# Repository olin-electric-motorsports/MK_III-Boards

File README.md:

# MK_III-Boards
Kicad files for our boards for the 2017-2018 Competition season.

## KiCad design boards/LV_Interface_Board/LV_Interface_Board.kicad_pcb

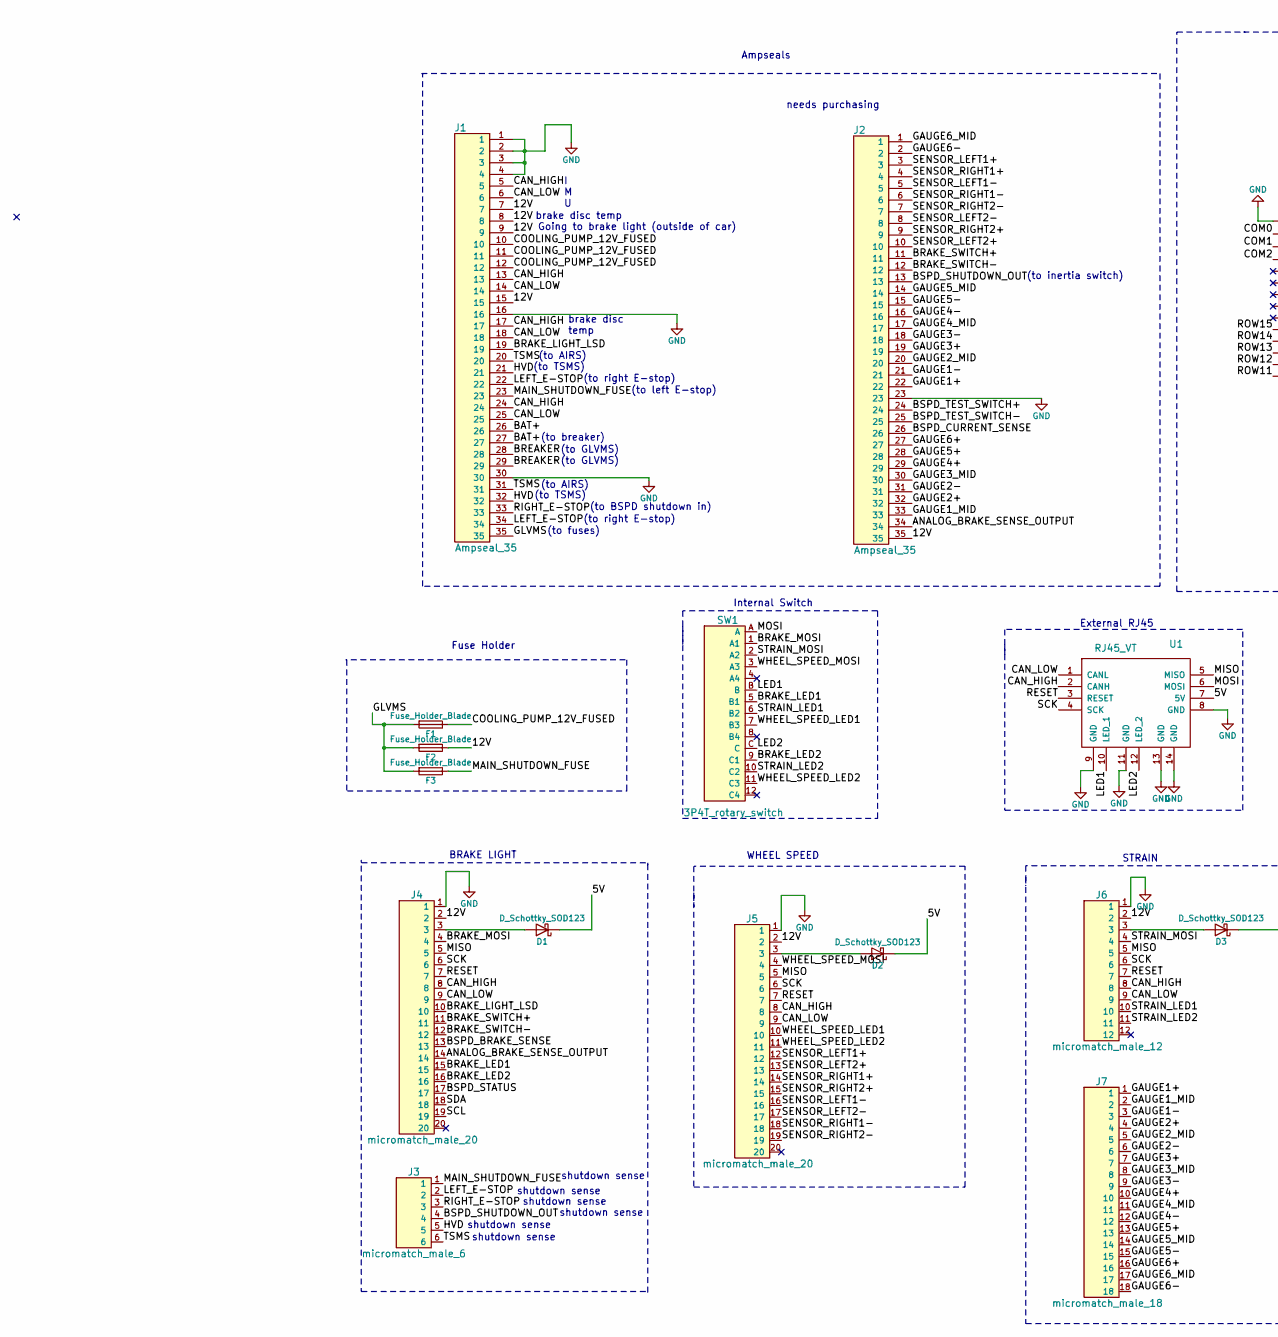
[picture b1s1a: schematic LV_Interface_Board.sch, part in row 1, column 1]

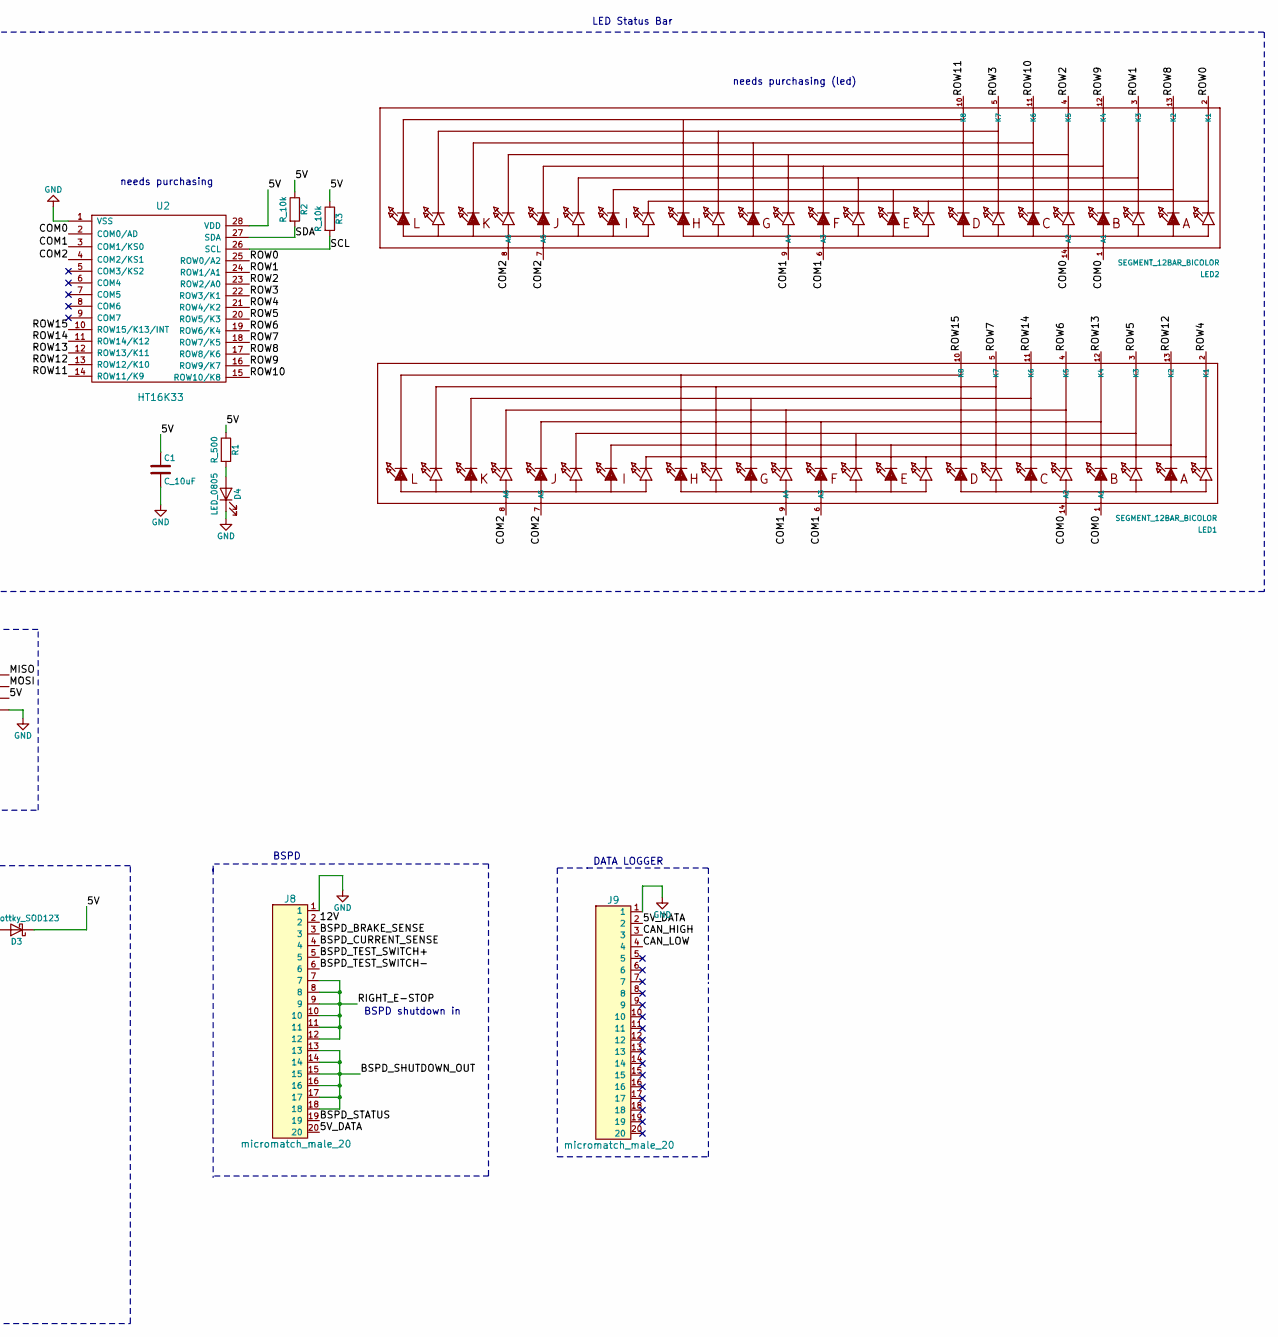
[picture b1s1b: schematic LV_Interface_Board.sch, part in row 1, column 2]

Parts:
C1: C_10uF; C_0805_OEM; MPN 478-5167-1-ND
D1, D2, D3: D_Schottky_SOD123; D_SOD-123W_OEM; MPN 1727-2394-1-ND
D4: LED_0805; LED_0805_OEM; MPN 475-1410-1-ND
F1, F2, F3: Fuse_Holder_Blade; fuse_block_holder; MPN 36-3557-2-ND
J1, J2: Ampseal_35
J3: micromatch_male_6; micromatch_female_ra_6; MPN A107035CT-ND
J4, J5, J8, J9: micromatch_male_20; micromatch_female_ra_20; MPN A111126CT-ND
J6: micromatch_male_12; micromatch_female_ra_12; MPN A110882CT-ND
J7: micromatch_male_18; micromatch_female_ra_18; MPN A110884CT-ND
LED1, LED2: SEGMENT_12BAR_BICOLOR; SEGMENT_BICOL_BL-AR12Z3010
R1: R_500; R_0805_OEM; MPN 541-1905-2-ND
R2, R3: R_10k; R_0805_OEM; MPN CRS0805-FX-1002ELFCT-ND
SW1: 3P4T_rotary_switch; MPN s14100400am2451
U1: RJ45_VT; RJ45-Vertical
U2: HT16K33; SOP28

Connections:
/5V: C1.1, D1.1 (K), D2.1 (K), D3.1 (K), R1.1, R2.1, R3.1, U1.7 (5V), U2.28 (VDD)
/5V_DATA: J8.20, J9.2
/12V: F2.1, J1.7, J1.8, J1.9, J1.15, J2.35, J4.2, J5.2, J6.2, J8.2
/ANALOG_BRAKE_SENSE_OUTPUT: J2.34, J4.14
/BAT+: J1.26, J1.27
/BRAKE_LED1: J4.15, SW1.5 (B1)
/BRAKE_LED2: J4.16, SW1.9 (C1)
/BRAKE_LIGHT_LSD: J1.19, J4.10
/BRAKE_MOSI: J4.4, SW1.1 (A1)
/BRAKE_SWITCH+: J2.11, J4.11
/BRAKE_SWITCH-: J2.12, J4.12
/BREAKER: J1.28, J1.29
/BSPD_BRAKE_SENSE: J4.13, J8.3
/BSPD_CURRENT_SENSE: J2.26, J8.4
/BSPD_SHUTDOWN_OUT: J2.13, J3.4, J8.13, J8.14, J8.15, J8.16, J8.17, J8.18
/BSPD_STATUS: J4.17, J8.19
/BSPD_TEST_SWITCH+: J2.24, J8.5
/BSPD_TEST_SWITCH-: J2.25, J8.6
/CAN_HIGH: J1.5, J1.13, J1.17, J1.24, J4.8, J5.8, J6.8, J9.3, U1.2 (CANH)
/CAN_LOW: J1.6, J1.14, J1.18, J1.25, J4.9, J5.9, J6.9, J9.4, U1.1 (CANL)
/COM0: LED1.1 (A1), LED1.14 (A2), LED2.1 (A1), LED2.14 (A2), U2.2 (COM0/AD)
/COM1: LED1.6 (A3), LED1.9 (A4), LED2.6 (A3), LED2.9 (A4), U2.3 (COM1/KS0)
/COM2: LED1.7 (A5), LED1.8 (A6), LED2.7 (A5), LED2.8 (A6), U2.4 (COM2/KS1)
/COOLING_PUMP_12V_FUSED: F1.1, J1.10, J1.11, J1.12
/GAUGE1+: J2.22, J7.1
/GAUGE1-: J2.21, J7.3
/GAUGE1_MID: J2.33, J7.2
/GAUGE2+: J2.32, J7.4
/GAUGE2-: J2.31, J7.6
/GAUGE2_MID: J2.20, J7.5
/GAUGE3+: J2.19, J7.7
/GAUGE3-: J2.18, J7.9
/GAUGE3_MID: J2.30, J7.8
/GAUGE4+: J2.29, J7.10
/GAUGE4-: J2.16, J7.12
/GAUGE4_MID: J2.17, J7.11
/GAUGE5+: J2.28, J7.13
/GAUGE5-: J2.15, J7.15
/GAUGE5_MID: J2.14, J7.14
/GAUGE6+: J2.27, J7.16
/GAUGE6-: J2.2, J7.18
/GAUGE6_MID: J2.1, J7.17
/GLVMS: F1.2, F2.2, F3.2, J1.35
/HVD: J1.21, J1.32, J3.5
/LED1: SW1.B, U1.10 (LED_1)
/LED2: SW1.C, U1.12 (LED_2)
/LEFT_E-STOP: J1.22, J1.34, J3.2
/MAIN_SHUTDOWN_FUSE: F3.1, J1.23, J3.1
/MISO: J4.5, J5.5, J6.5, U1.5 (MISO)
/MOSI: SW1.A, U1.6 (MOSI)
/RESET: J4.7, J5.7, J6.7, U1.3 (RESET)
/RIGHT_E-STOP: J1.33, J3.3, J8.7, J8.8, J8.9, J8.10, J8.11, J8.12
/ROW0: LED2.2 (K1), U2.25 (ROW0/A2)
/ROW1: LED2.3 (K3), U2.24 (ROW1/A1)
/ROW2: LED2.4 (K5), U2.23 (ROW2/A0)
/ROW3: LED2.5 (K7), U2.22 (ROW3/K1)
/ROW4: LED1.2 (K1), U2.21 (ROW4/K2)
/ROW5: LED1.3 (K3), U2.20 (ROW5/K3)
/ROW6: LED1.4 (K5), U2.19 (ROW6/K4)
/ROW7: LED1.5 (K7), U2.18 (ROW7/K5)
/ROW8: LED2.13 (K2), U2.17 (ROW8/K6)
/ROW9: LED2.12 (K4), U2.16 (ROW9/K7)
/ROW10: LED2.11 (K6), U2.15 (ROW10/K8)
/ROW11: LED2.10 (K8), U2.14 (ROW11/K9)
/ROW12: LED1.13 (K2), U2.13 (ROW12/K10)
/ROW13: LED1.12 (K4), U2.12 (ROW13/K11)
/ROW14: LED1.11 (K6), U2.11 (ROW14/K12)
/ROW15: LED1.10 (K8), U2.10 (ROW15/K13/INT)
/SCK: J4.6, J5.6, J6.6, U1.4 (SCK)
/SCL: J4.19, R3.2, U2.26 (SCL)
/SDA: J4.18, R2.2, U2.27 (SDA)
/SENSOR_LEFT1+: J2.3, J5.12
/SENSOR_LEFT1-: J2.5, J5.16
/SENSOR_LEFT2+: J2.10, J5.13
/SENSOR_LEFT2-: J2.8, J5.17
/SENSOR_RIGHT1+: J2.4, J5.14
/SENSOR_RIGHT1-: J2.6, J5.18
/SENSOR_RIGHT2+: J2.9, J5.15
/SENSOR_RIGHT2-: J2.7, J5.19
/STRAIN_LED1: J6.10, SW1.6 (B2)
/STRAIN_LED2: J6.11, SW1.10 (C2)
/STRAIN_MOSI: J6.4, SW1.2 (A2)
/TSMS: J1.20, J1.31, J3.6
/WHEEL_SPEED_LED1: J5.10, SW1.7 (B3)
/WHEEL_SPEED_LED2: J5.11, SW1.11 (C3)
/WHEEL_SPEED_MOSI: J5.4, SW1.3 (A3)
GND: C1.2, D4.1 (K), J1.1, J1.2, J1.3, J1.4, J1.16, J1.30, J2.23, J4.1, J5.1, J6.1, J8.1, J9.1, U1.8 (GND), U1.9 (GND), U1.11 (GND), U1.13 (GND), U1.14 (GND), U2.1 (VSS)
unnamed: D1.2 (A), J4.3
unnamed: D2.2 (A), J5.3
unnamed: D3.2 (A), J6.3
unnamed: D4.2 (A), R1.2

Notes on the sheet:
DATA LOGGER
STRAIN
BSPD
WHEEL SPEED
BRAKE LIGHT
Internal Switch
External RJ45
(to inertia switch)
(to breaker)
(to GLVMS) (to GLVMS)
(to left E-stop)
(to right E-stop)
(to TSMS)
(to AIRS)
(to BSPD shutdown in)
(to fuses)
shutdown sense
brake disc temp
I M U
brake disc temp
Fuse Holder
Going to brake light (outside of car)
Ampseals
LED Status Bar
BSPD shutdown in
needs purchasing
needs purchasing (led)

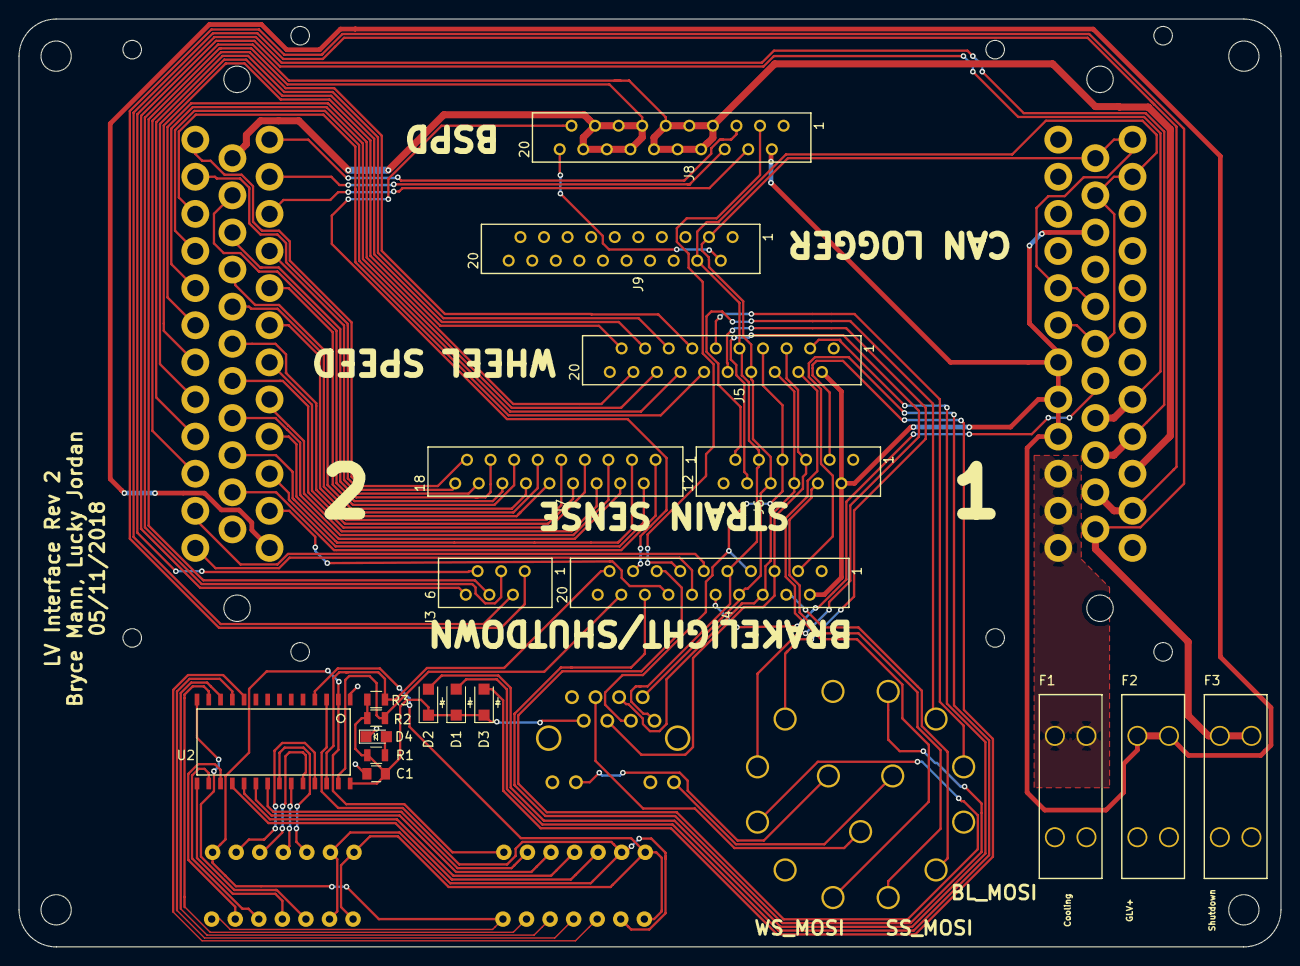
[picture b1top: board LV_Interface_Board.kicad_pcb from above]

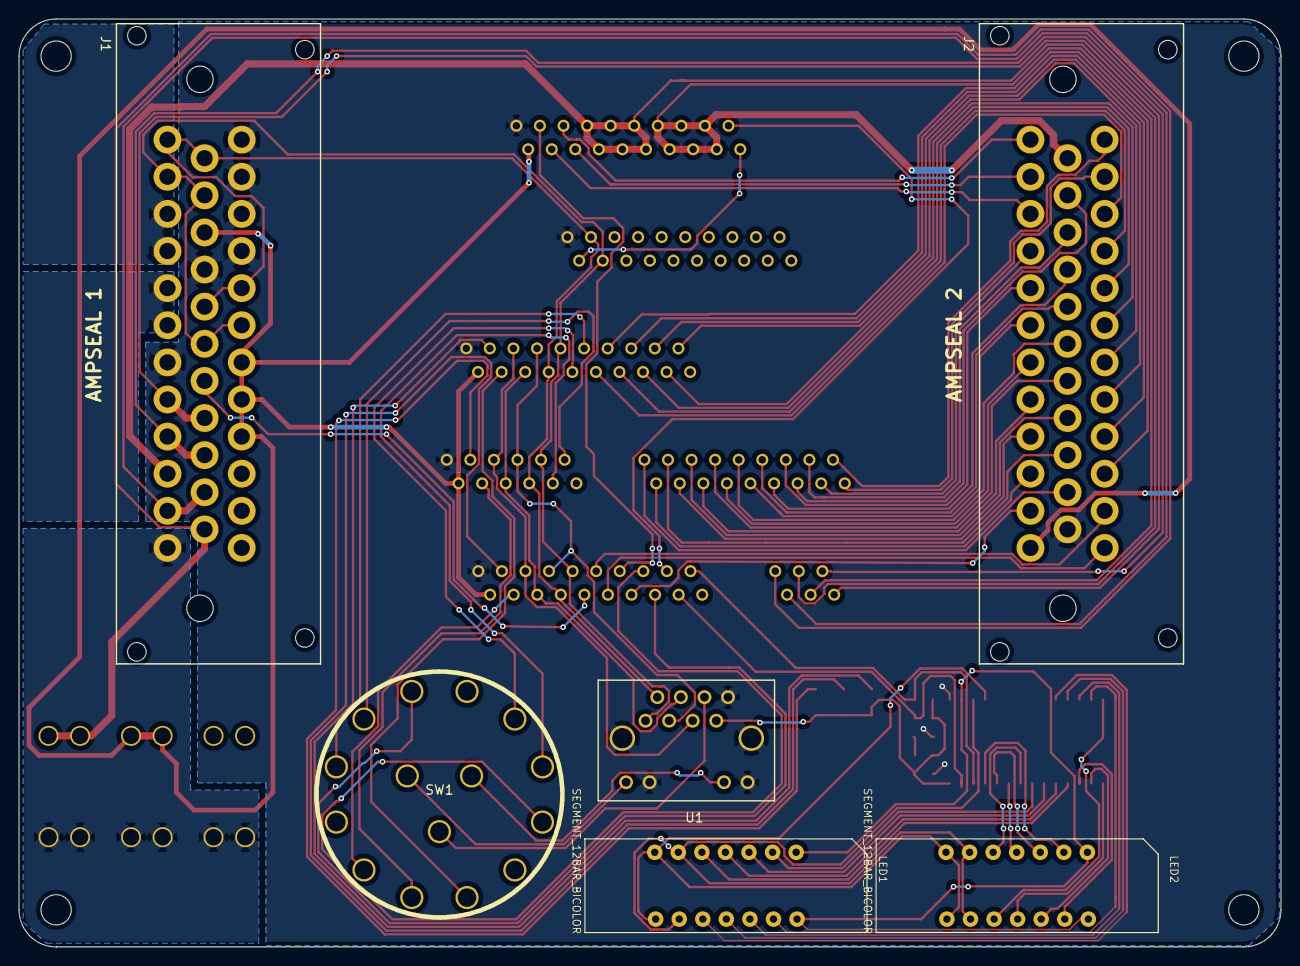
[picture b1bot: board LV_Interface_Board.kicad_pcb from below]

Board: 2 copper layers, 136.0 x 100.0 mm, 25 parts (6 on the bottom side), 91 nets.

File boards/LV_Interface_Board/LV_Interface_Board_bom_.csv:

Component,Description,Part,References,Value,Footprint,Quantity Per PCB,Datasheet,Package,MPN,MFN,PurchasingLink
1,CAP CER 10UF 10V X5R 0805,C_10uF,C1,C_10uF,C_0805_OEM,1,http://datasheets.avx.com/cx5r.pdf,Value,478-5167-1-ND,Digi-Key,https://www.digikey.com/product-detail/en/avx-corporation/08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
2,DIODE SCHOTTKY 100V 1A SOD123,D_Schottky_SOD123,D1 D2 D3,D_Schottky_SOD123,D_SOD-123W_OEM,3,https://assets.nexperia.com/documents/data-sheet/PMEG10010ELR.pdf,,1727-2394-1-ND,Digi-Key,https://www.digikey.com/product-detail/en/nexperia-usa-inc/P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
3,LED_0805,LED_0805,D4,LED_0805,LED_0805_OEM,1,http://www.osram-os.com/Graphics/XPic9/00078860_0.pdf,Value,475-1410-1-ND,Digi-Key,https://www.digikey.com/products/en?keywords=475-1410-1-ND
4,fuse block,fuse_holder_125V_15A,F1,fuse_holder_125V_15A,fuse_block,1,http://www.littelfuse.com/~/media/electronics/datasheets/res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,Value,F5764CT-ND,Digi-Key,https://www.digikey.com/products/en/circuit-protection/fuseh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
5,Waterproof Panel-Mount Connector RA 35-Pin,Ampseal_35,J1 J2,Ampseal_35,Ampseal_35,2,http://www.te.com/commerce/DocumentDelivery/DDEController?Ac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,,,,
6,connector micromatch male 12,micromatch_male_12,J6,micromatch_male_12,micromatch_female_ra_12,1,,Value,A110882CT-ND,Digi-Key,https://www.digikey.com/product-detail/en/te-connectivity-am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
7,connector micromatch male 18,micromatch_male_18,J7,micromatch_male_18,micromatch_female_ra_18,1,,Value,A110884CT-ND,Digi-Key,https://www.digikey.com/product-detail/en/te-connectivity-am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
8,connector micromatch male 20,micromatch_male_20,J4 J5 J8 J9,micromatch_male_20,micromatch_female_ra_20,4,,Value,A111126CT-ND,Digi-Key,https://www.digikey.com/product-detail/en/te-connectivity-am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
9,connector micromatch male 6,micromatch_male_6,J3,micromatch_male_6,micromatch_female_ra_6,1,,Value,A107035CT-ND,Digi-Key,https://www.digikey.com/product-detail/en/te-connectivity-am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
10,,SEGMENT_12BAR_BICOLOR,LED1 LED2,SEGMENT_12BAR_BICOLOR,SEGMENT_BICOL_BL-AR12Z3010,2,,,,,
11,Res 10k 1%,R_10k,R2 R3,R_10k,R_0805_OEM,2,http://www.bourns.com/data/global/pdfs/CRS.pdf,Value,CRS0805-FX-1002ELFCT-ND,Digi-Key,https://www.digikey.com/products/en?keywords=CRS0805-FX-1002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
12,Resistor 500Ohm 0.1% Tolerance,R_500,R1,R_500,R_0805_OEM,1,http://www.vishay.com/docs/60057/pnm.pdf,Value,541-1905-2-ND,Digi Key,https://www.digikey.com/product-detail/en/vishay-dale/PNM040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
13,3P4T rotary switch,3P4T_rotary_switch,SW1,3P4T_rotary_switch,3P4T_rotary_switch,1,,Value,s14100400am2451,Uxcell,https://www.amazon.com/Single-Rotary-Switch-Selector-Positio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
14,,HT16K33,U2,HT16K33,SOP28,1,,,,,
15,CONN MOD JACK 8P8C VERT UNSHLD,RJ45_VT,U1,RJ45_VT,RJ45-Vertical,1,https://www.amphenolcanada.com/ProductSearch/drawings/AC/MRJ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,,,,https://www.digikey.com/products/en?keywords=MRJ-5481-01





Component Groups:,15
Component Count:,23
Fitted Components:,23
Number of PCBs:,1
Total components:,23
Schematic Version:,
Schematic Date:,
BoM Date:,Mon 26 Feb 2018 10:05:01 PM EST
Schematic Source:,/home/bryce/Storage/Formula/Boards/boards/LV_Interface_Board/LV_Interface_Board.sch
KiCad Version:,Eeschema 4.0.2+dfsg1-stable

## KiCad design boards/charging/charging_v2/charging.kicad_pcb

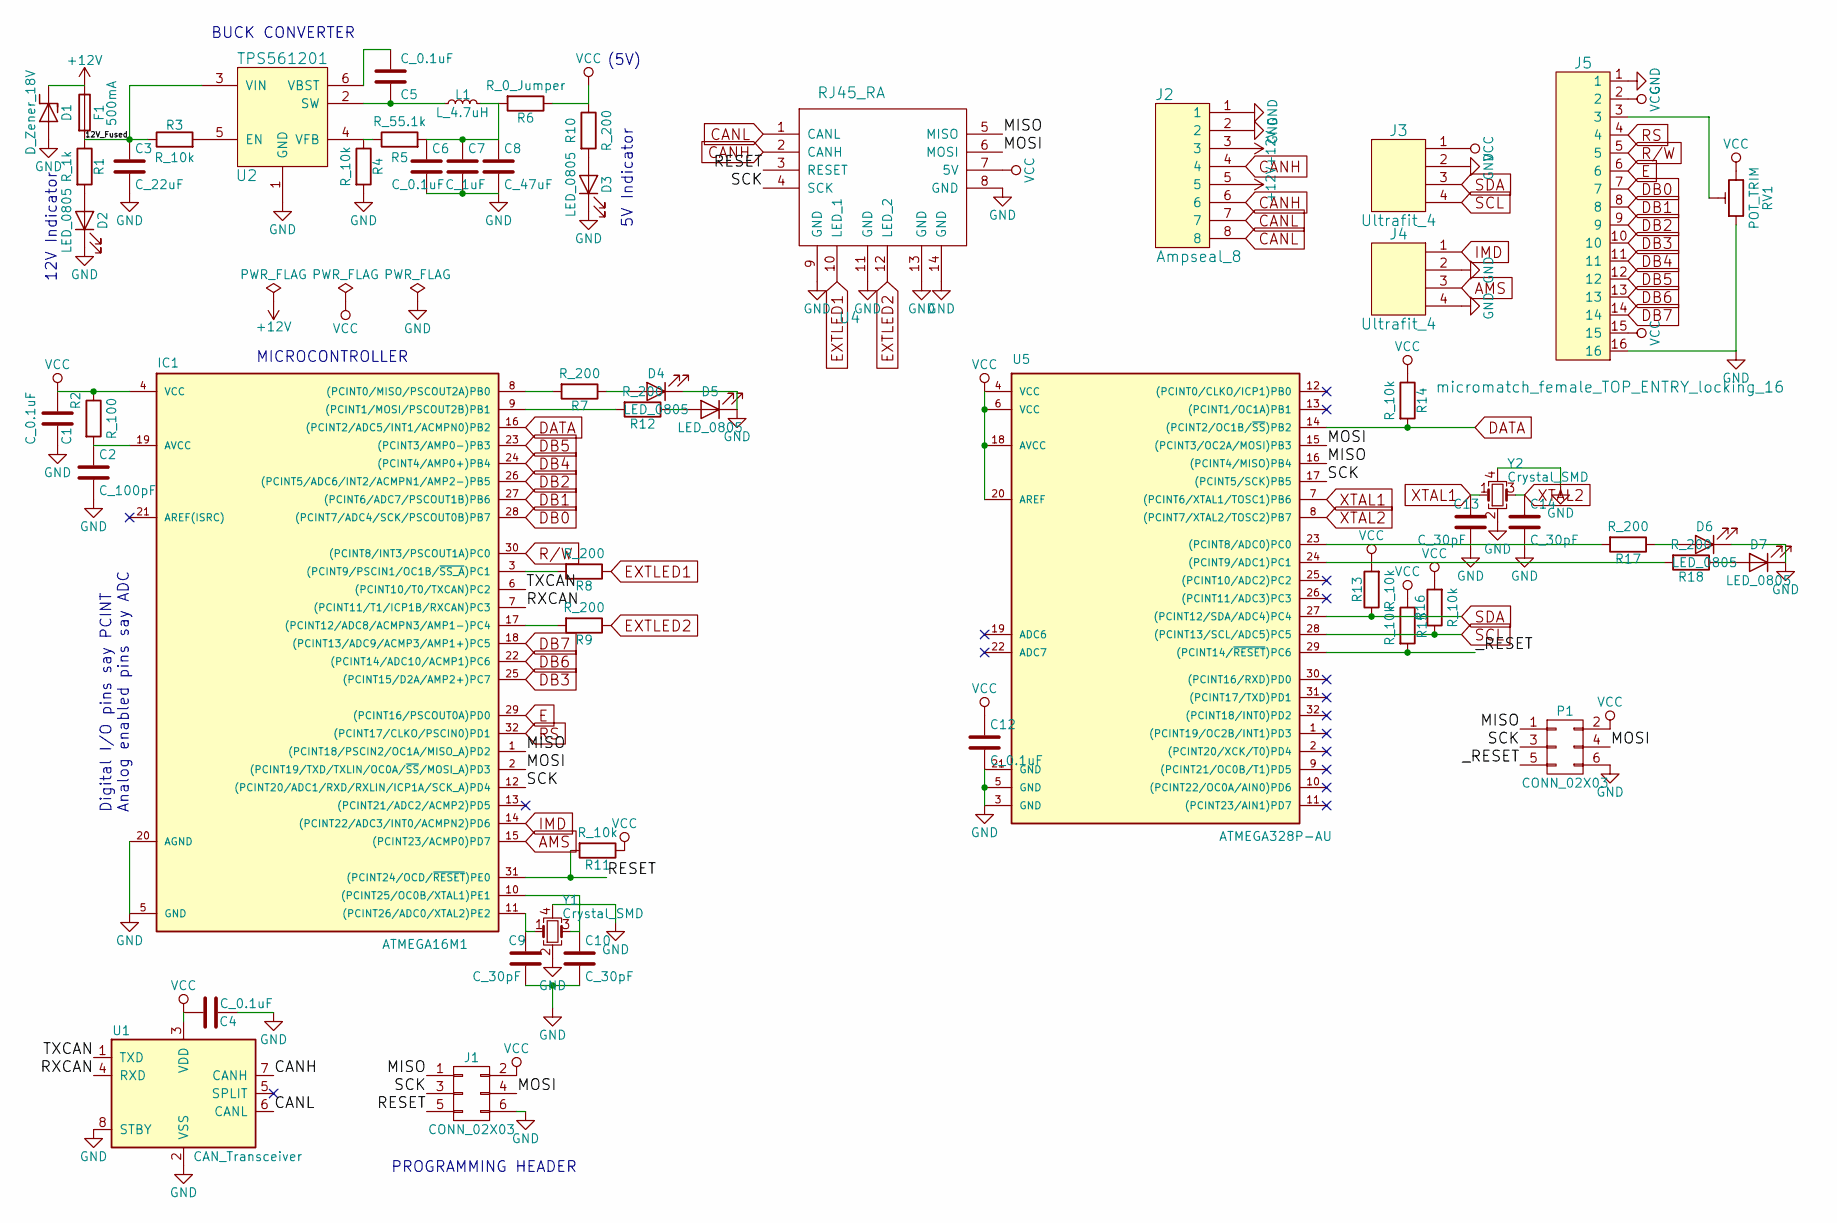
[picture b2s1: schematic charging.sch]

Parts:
C1, C4, C5: C_0.1uF; C_0805; MPN 478-3352-1-ND
C2: C_100pF; C_0805; MPN 399-1122-1-ND
C3: C_22uF; C_1206; MPN 1276-2725-1-ND
C6, C12: C_0.1uF; C_0805_OEM; MPN 478-3352-1-ND
C7: C_1uF; C_0805_OEM; MPN 478-10487-1-ND
C8: C_47uF; C_0805; MPN 587-4280-1-ND
C9, C10, C13, C14: C_30pF; C_0805; MPN 1276-1130-1-ND
D1: D_Zener_18V; DO-214AA; MPN SMBJ5355B-TPMSCT-ND
D2, D3: LED_0805; MPN 475-1410-1-ND
D4, D5, D6, D7: LED_0805; LED_0805_OEM; MPN 475-1410-1-ND
F1: 500mA; Fuse_1210; MPN 507-1786-1-ND
IC1: ATMEGA16M1; TQFP-32_7x7mm_Pitch0.8mm; MPN ATMEGA16M1-AU-ND
J1: CONN_02X03; Pin_Header_Straight_2x03; MPN 609-3234-ND
J2: Ampseal_8; MPN MRJ-5381-01-ND
J3, J4: Ultrafit_4; MPN WM11574-ND
J5: micromatch_female_TOP_ENTRY_locking_16; micromatch_female_vert_16; MPN A99501CT-ND
L1: L_4.7uH; 4.7uH_Inductor_OEM; MPN 445-6583-1-ND
P1: CONN_02X03; Pin_Header_Straight_2x03; MPN 609-3234-ND
R1: R_1k; R_0805; MPN RNCP0805FTD1K00CT-ND
R2: R_100; R_0805; MPN RNCP0805FTD100RCT-ND
R3, R4, R11: R_10k; R_0805; MPN CRS0805-FX-1002ELFCT-ND
R5: R_55.1k; R_0805; MPN 311-51.1KCRCT-ND
R6: R_0_Jumper; R_2512; MPN A121322CT-ND
R7, R8, R9, R12, R17, R18: R_200; R_0805_OEM; MPN RMCF0805JT200RCT-ND
R10: R_200; R_0805; MPN RMCF0805JT200RCT-ND
R13, R14, R15, R16: R_10k; R_0805_OEM; MPN CRS0805-FX-1002ELFCT-ND
RV1: POT_TRIM; Potentiometer_Trimmer_Bourns_TCC3
U1: CAN_Transceiver; SOIC-8_3.9x4.9mm_Pitch1.27mm; MPN MCP2561-E/SN-ND
U2: TPS561201; SOT-23-6; MPN TPS561201
U4: RJ45_RA; RJ45-RightAngle
U5: ATMEGA328P-AU; TQFP-32_7x7mm_Pitch0.8mm
Y1, Y2: Crystal_SMD; Crystal_SMD_FA238; MPN SER3686CT-ND

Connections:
+12V: D1.1 (K), F1.1, J2.3, J2.5
/12V_Fused: C3.1, F1.2, R1.1, R3.1, U2.3 (VIN)
/MISO: IC1.1 ((PCINT18/PSCIN2/OC1A/MISO_A)PD2), J1.1, P1.1, U4.5 (MISO), U5.16 ((PCINT4/MISO)PB4)
/MOSI: IC1.2 ((PCINT19/TXD/TXLIN/OC0A/~SS~/MOSI_A)PD3), J1.4, P1.4, U4.6 (MOSI), U5.15 ((PCINT3/OC2A/MOSI)PB3)
/RESET: IC1.31 ((PCINT24/OCD/~RESET~)PE0), J1.5, R11.2, U4.3 (RESET)
/RXCAN: IC1.7 ((PCINT11/T1/ICP1B/RXCAN)PC3), U1.4 (RXD)
/SCK: IC1.12 ((PCINT20/ADC1/RXD/RXLIN/ICP1A/SCK_A)PD4), J1.3, P1.3, U4.4 (SCK), U5.17 ((PCINT5/SCK)PB5)
/TXCAN: IC1.6 ((PCINT10/T0/TXCAN)PC2), U1.1 (TXD)
/_RESET: P1.5, R15.2, U5.29 ((PCINT14/~RESET~)PC6)
AMS: IC1.15 ((PCINT23/ACMP0)PD7), J4.3
CANH: J2.4, J2.6, U1.7 (CANH), U4.2 (CANH)
CANL: J2.7, J2.8, U1.6 (CANL), U4.1 (CANL)
DATA: IC1.16 ((PCINT2/ADC5/INT1/ACMPN0)PB2), R14.2, U5.14 ((PCINT2/OC1B/~SS~)PB2)
DB0: IC1.28 ((PCINT7/ADC4/SCK/PSCOUT0B)PB7), J5.7
DB1: IC1.27 ((PCINT6/ADC7/PSCOUT1B)PB6), J5.8
DB2: IC1.26 ((PCINT5/ADC6/INT2/ACMPN1/AMP2-)PB5), J5.9
DB3: IC1.25 ((PCINT15/D2A/AMP2+)PC7), J5.10
DB4: IC1.24 ((PCINT4/AMP0+)PB4), J5.11
DB5: IC1.23 ((PCINT3/AMP0-)PB3), J5.12
DB6: IC1.22 ((PCINT14/ADC10/ACMP1)PC6), J5.13
DB7: IC1.18 ((PCINT13/ADC9/ACMP3/AMP1+)PC5), J5.14
E: IC1.29 ((PCINT16/PSCOUT0A)PD0), J5.6
EXTLED1: R8.1, U4.10 (LED_1)
EXTLED2: R9.1, U4.12 (LED_2)
GND: C1.2, C2.2, C3.2, C4.2, C6.2, C7.2, C8.2, C9.2, C10.2, C12.2, C13.2, C14.2, D1.2 (A), D2.1 (K), D3.1 (K), D4.1 (K), D5.1 (K), D6.1 (K), D7.1 (K), IC1.5 (GND), IC1.20 (AGND), J1.6, J2.1, J2.2, J3.2, J4.2, J4.4, J5.1, J5.16, P1.6, R4.2, RV1.1, U1.2 (VSS), U1.8 (STBY), U2.1 (GND), U4.8 (GND), U4.9 (GND), U4.11 (GND), U4.13 (GND), U4.14 (GND), U5.3 (GND), U5.5 (GND), U5.21 (GND), Y1.2, Y1.4, Y2.2, Y2.4
IMD: IC1.14 ((PCINT22/ADC3/INT0/ACMPN2)PD6), J4.1
unnamed: C2.1, IC1.19 (AVCC), R2.2
unnamed: C5.1, U2.6 (VBST)
unnamed: C5.2, L1.1, U2.2 (SW)
unnamed: C6.1, C7.1, C8.1, L1.2, R5.2, R6.2
unnamed: C9.1, IC1.11 ((PCINT26/ADC0/XTAL2)PE2), Y1.1
unnamed: C10.1, IC1.10 ((PCINT25/OC0B/XTAL1)PE1), Y1.3
unnamed: D2.2 (A), R1.2
unnamed: D3.2 (A), R10.2
unnamed: D4.2 (A), R7.1
unnamed: D5.2 (A), R12.1
unnamed: D6.2 (A), R17.1
unnamed: D7.2 (A), R18.1
unnamed: IC1.3 ((PCINT9/PSCIN1/OC1B/~SS_A~)PC1), R8.2
unnamed: IC1.8 ((PCINT0/MISO/PSCOUT2A)PB0), R7.2
unnamed: IC1.9 ((PCINT1/MOSI/PSCOUT2B)PB1), R12.2
unnamed: IC1.17 ((PCINT12/ADC8/ACMPN3/AMP1-)PC4), R9.2
unnamed: J5.3, RV1.2
unnamed: R3.2, U2.5 (EN)
unnamed: R4.1, R5.1, U2.4 (VFB)
unnamed: R17.2, U5.23 ((PCINT8/ADC0)PC0)
R/W: IC1.30 ((PCINT8/INT3/PSCOUT1A)PC0), J5.5
RS: IC1.32 ((PCINT17/CLKO/PSCIN0)PD1), J5.4
SCL: J3.4, R16.1, U5.28 ((PCINT13/SCL/ADC5)PC5)
SDA: J3.3, R13.1, U5.27 ((PCINT12/SDA/ADC4)PC4)
XTAL1: C13.1, U5.7 ((PCINT6/XTAL1/TOSC1)PB6), Y2.1
XTAL2: C14.1, U5.8 ((PCINT7/XTAL2/TOSC2)PB7), Y2.3

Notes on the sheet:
BUCK CONVERTER
12V Indicator
5V Indicator
(5V)
MICROCONTROLLER
PROGRAMMING HEADER
Digital I/O pins say PCINT Analog enabled pins say ADC

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
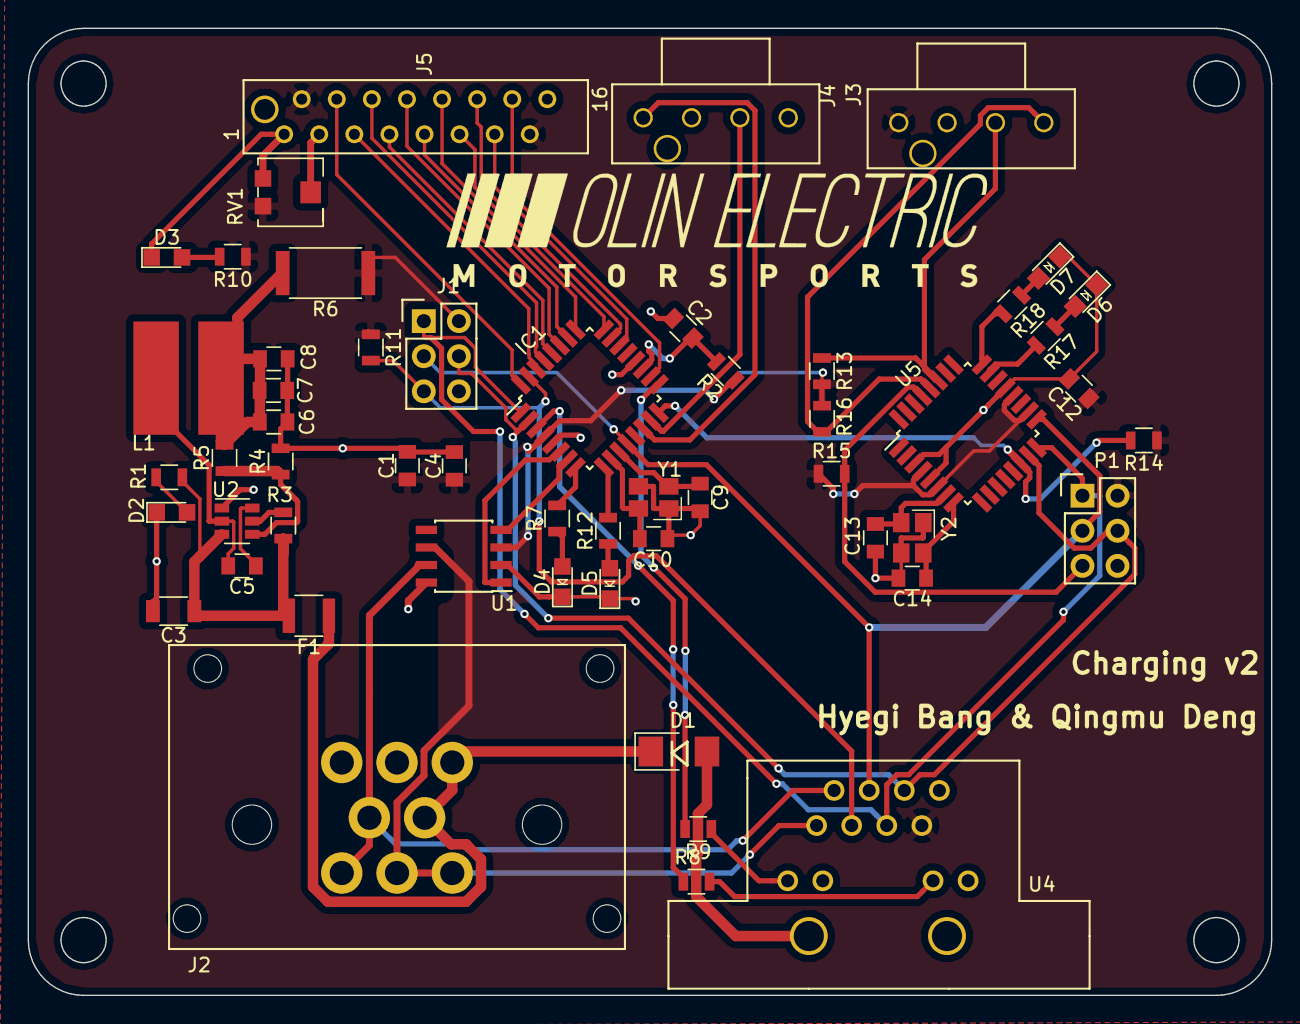
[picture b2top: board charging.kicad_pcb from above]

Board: 2 copper layers, 90.0 x 70.0 mm, 54 parts (0 on the bottom side), 54 nets.

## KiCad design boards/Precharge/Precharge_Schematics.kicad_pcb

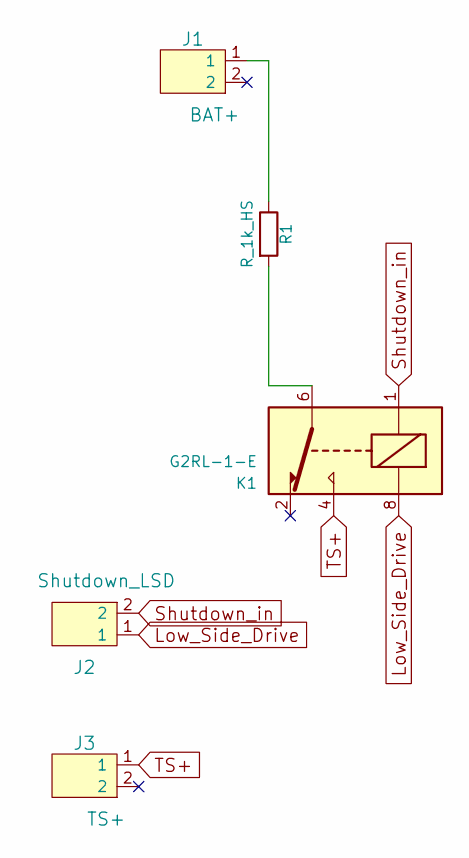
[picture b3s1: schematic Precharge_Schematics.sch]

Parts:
J1: BAT+; Ultrafit_2; MPN WM11570-ND
J2: Shutdown_LSD; Ultrafit_2; MPN WM11570-ND
J3: TS+; Ultrafit_2; MPN WM11570-ND
K1: G2RL-1-E; Relay_SPDT_OMRON-G2RL-1-E; MPN Z2834-ND
R1: R_1k_HS; R_3k_HS_TO247; MPN 696-1105-5-ND

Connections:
Low_Side_Drive: J2.1, K1.8
unnamed: J1.1, R1.1
unnamed: K1.6, R1.2
Shutdown_in: J2.2, K1.1
TS+: J3.1, K1.4

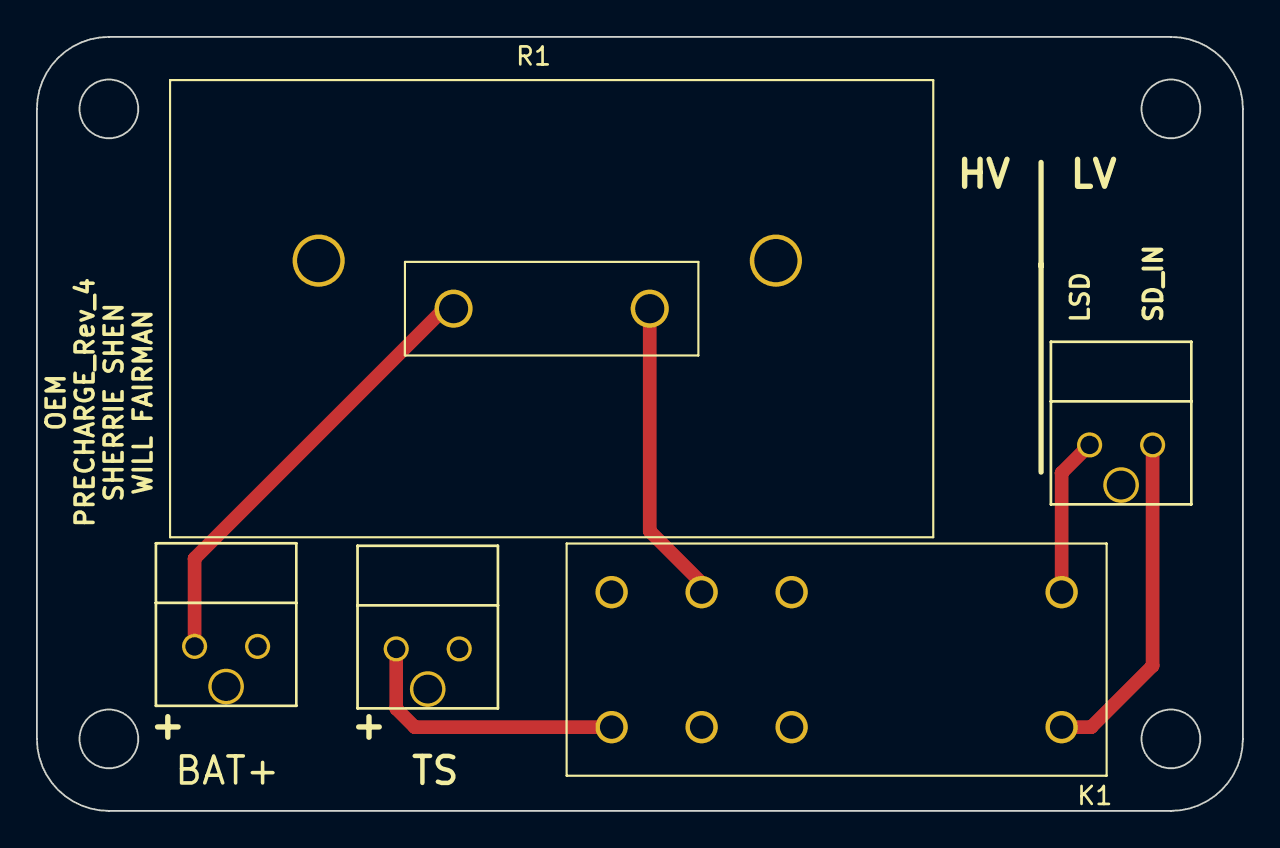
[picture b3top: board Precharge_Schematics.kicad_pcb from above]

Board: 2 copper layers, 67.0 x 43.0 mm, 5 parts (0 on the bottom side), 5 nets.

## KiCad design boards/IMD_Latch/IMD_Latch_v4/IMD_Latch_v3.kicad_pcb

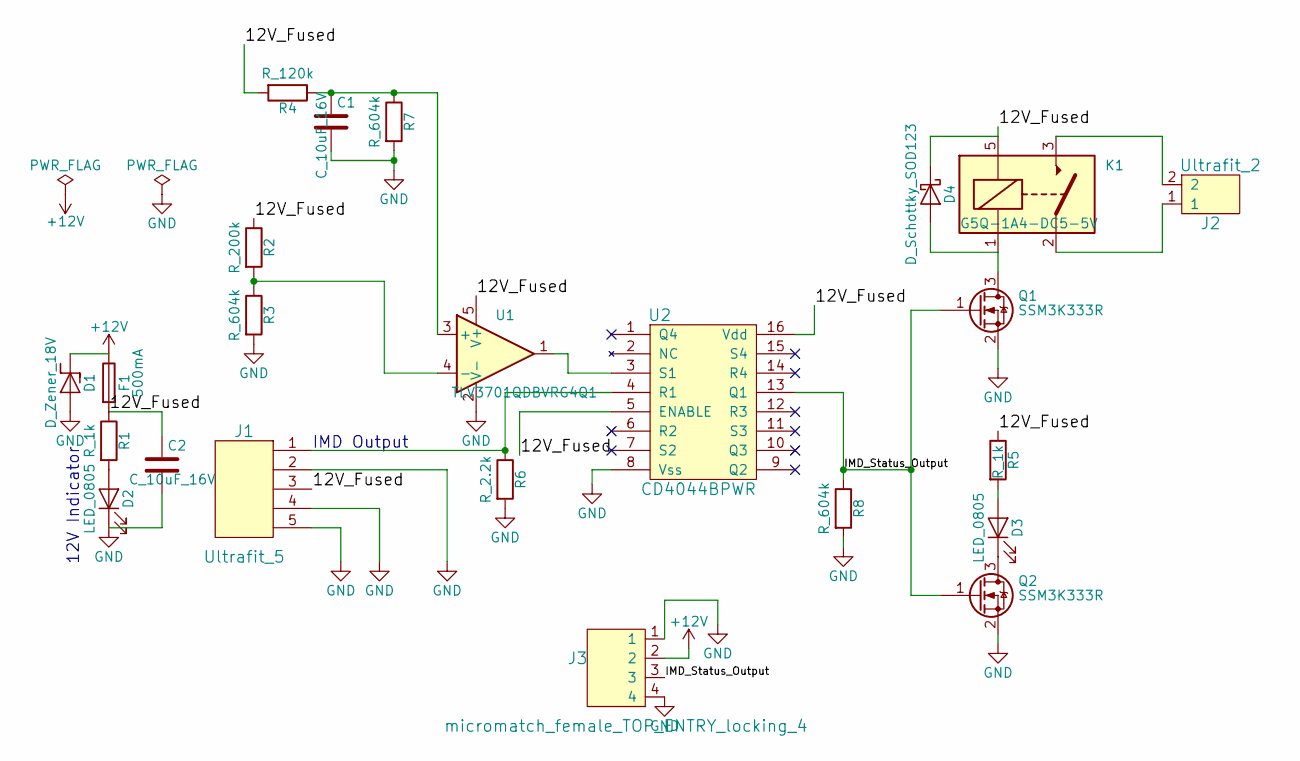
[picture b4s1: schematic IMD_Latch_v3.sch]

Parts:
C1, C2: C_10uF_16V; C_0805_OEM; MPN 1276-2399-1-ND
D1: D_Zener_18V; DO-214AA; MPN SMBJ5355B-TPMSCT-ND
D2, D3: LED_0805; LED_0805_OEM; MPN 475-1410-1-ND
D4: D_Schottky_SOD123; D_SOD-123W_OEM; MPN 1727-2394-1-ND
F1: 500mA; Fuse_1210; MPN 507-1786-1-ND
J1: Ultrafit_5; MPN WM11667-ND
J2: Ultrafit_2; MPN WM11570-ND
J3: micromatch_female_TOP_ENTRY_locking_4; micromatch_female_vert_4; MPN 338068-4
K1: G5Q-1A4-DC5-5V; Relay_SPST_OMRON-G5Q-1A4_OEM; MPN Z3632-ND
Q1, Q2: SSM3K333R; SOT-23F; MPN SSM3K333RLFCT-ND
R1, R5: R_1k; R_0805_OEM; MPN RNCP0805FTD1K00CT-ND
R2: R_200k; R_0805_OEM; MPN RMCF0805FG200K
R3, R7, R8: R_604k; R_0805_OEM; MPN RMCF0805FT604KCT-ND
R4: R_120k; R_0805_OEM; MPN RMCF0805FT120KCT-ND
R6: R_2.2k; R_0805_OEM; MPN RMCF0805FT2K20CT-ND
U1: TLV3701QDBVRG4Q1; SOT-23-5_OEM; MPN 497-10249-1-ND
U2: CD4044BPWR; TSSOP-16-OEM; MPN 296-14106-1-ND

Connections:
+12V: D1.1 (K), F1.1, J3.2
/12V_Fused: C2.1, D4.1 (K), F1.2, J1.3, K1.5, R1.1, R2.1, R4.2, R5.1, U1.5 (V+), U2.5 (ENABLE), U2.16 (Vdd)
/IMD_Status_Output: J3.3, Q1.1 (G), Q2.1 (G), R8.1, U2.13 (Q1)
GND: C1.2, C2.2, D1.2 (A), D2.1 (K), J1.2, J1.4, J1.5, J3.1, J3.4, Q1.2 (S), Q2.2 (S), R3.2, R6.2, R7.2, R8.2, U1.2 (V-), U2.8 (Vss)
unnamed: C1.1, R4.1, R7.1, U1.3 (+)
unnamed: D2.2 (A), R1.2
unnamed: D3.1 (K), Q2.3 (D)
unnamed: D3.2 (A), R5.2
unnamed: D4.2 (A), K1.1, Q1.3 (D)
unnamed: J1.1, R6.1, U2.4 (R1)
unnamed: J2.1, K1.2
unnamed: J2.2, K1.3
unnamed: R2.2, R3.1, U1.4 (-)
unnamed: U1.1, U2.3 (S1)

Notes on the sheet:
12V Indicator
IMD Output

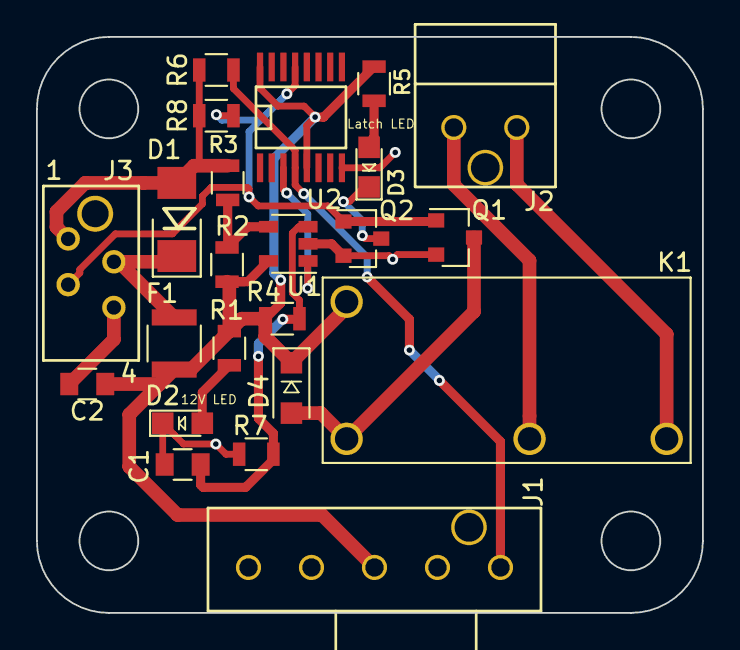
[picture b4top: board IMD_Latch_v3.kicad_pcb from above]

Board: 2 copper layers, 37.0 x 32.0 mm, 23 parts (0 on the bottom side), 14 nets.
